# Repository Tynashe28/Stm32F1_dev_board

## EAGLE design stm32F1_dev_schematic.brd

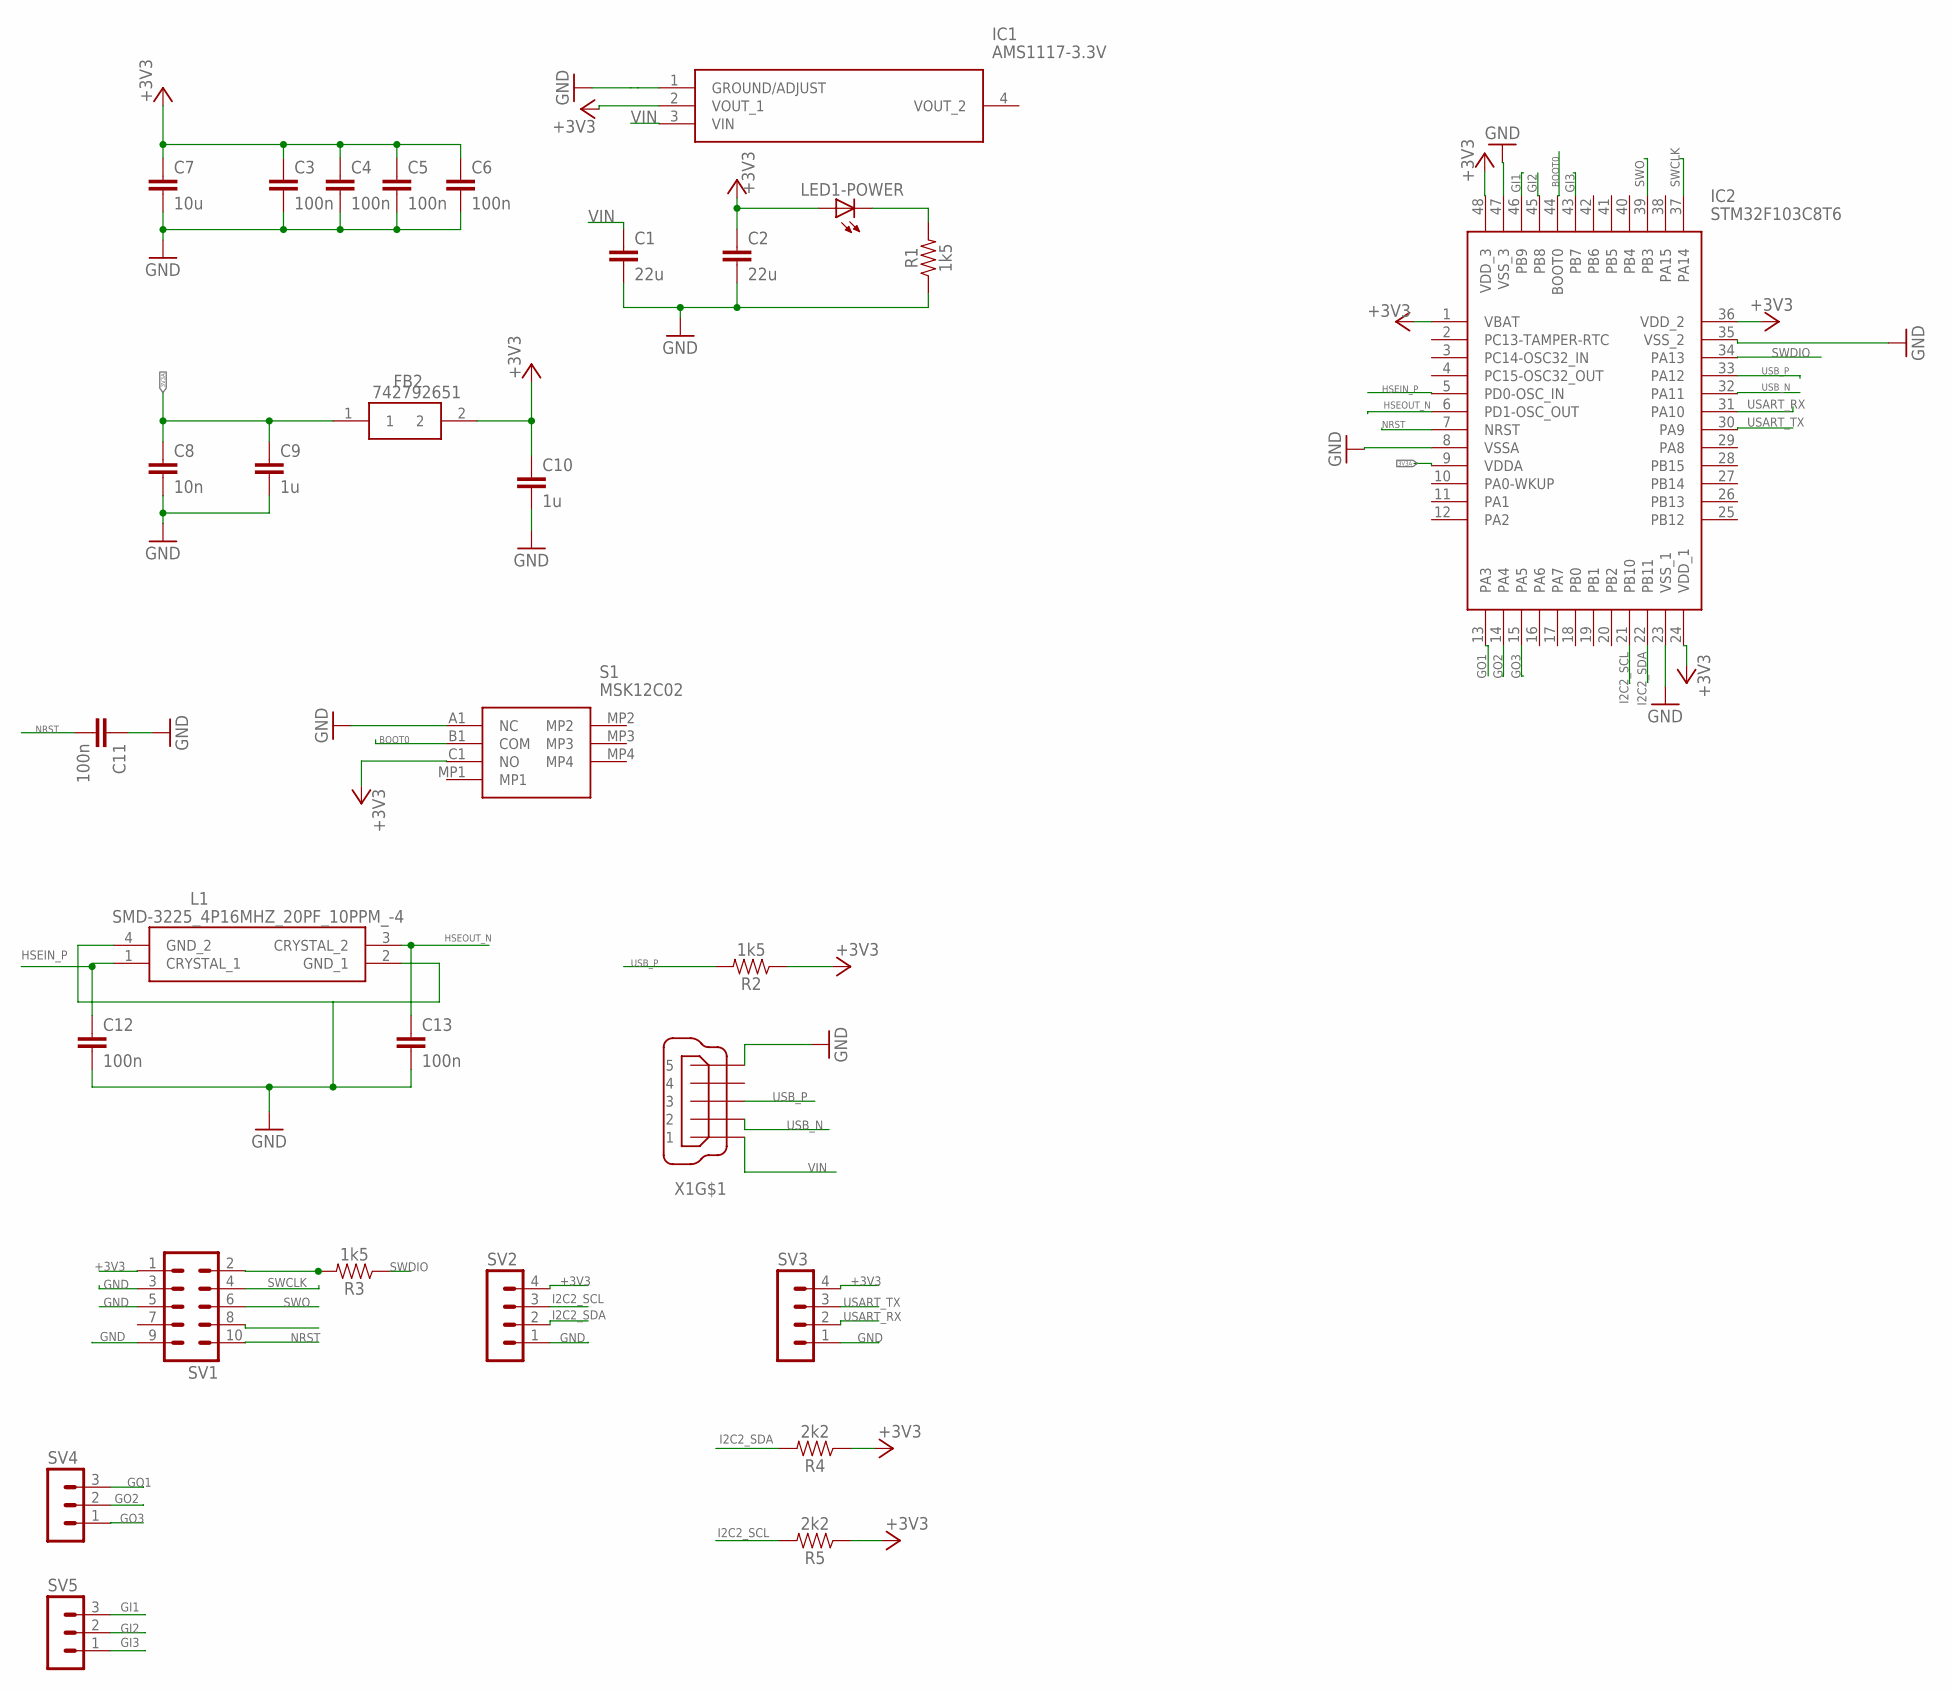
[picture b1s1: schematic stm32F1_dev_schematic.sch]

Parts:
C1, C2: 22u; 0805
C3, C4, C5, C6, C11, C12, C13: 100n; 0805
C7: 10u; 0805
C8: 10n; 0805
C9, C10: 1u; 0805
FB2: 742792651; BEADC1608X100N
IC1: AMS1117-3.3V; SOT229P700X180-4N
IC2: STM32F103C8T6; QFP50P900X900X160-48N
L1: SMD-3225_4P16MHZ_20PF_10PPM_-4; SMD3225_4P16MHZ20PF10PPM4085
LED1-POWER: LEDCHIPLED_0603; CHIPLED_0603
R1, R2, R3: 1k5; 0805
R4, R5: 2k2; 0805
S1: MSK12C02
SV1: MA05-2
SV2, SV3: MA04-1
SV4, SV5: MA03-1
X1: MINI-USB-SCHIELD-32005-301; 32005-301

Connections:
3V3A: C8.1, C9.1, FB2.1, IC2.9 (VDDA)
+3V3: C2.1, C3.1, C4.1, C5.1, C6.1, C7.1, C10.1, FB2.2, IC1.2 (VOUT_1), IC2.1 (VBAT), IC2.24 (VDD_1), IC2.36 (VDD_2), IC2.48 (VDD_3), LED1-POWER.A, R2.1, R4.1, R5.1, S1.C1 (NO), SV1.1, SV2.4, SV3.4
BOOT0: IC2.44 (BOOT0), S1.B1 (COM)
GI1: IC2.46 (PB9), SV5.3
GI2: IC2.45 (PB8), SV5.2
GI3: IC2.43 (PB7), SV5.1
GND: C1.2, C2.2, C3.2, C4.2, C5.2, C6.2, C7.2, C8.2, C9.2, C10.2, C11.1, C12.2, C13.2, IC1.1 (GROUND/ADJUST), IC2.8 (VSSA), IC2.23 (VSS_1), IC2.35 (VSS_2), IC2.47 (VSS_3), L1.2 (GND_1), L1.4 (GND_2), R1.1, S1.A1 (NC), SV1.3, SV1.5, SV1.9, SV2.1, SV3.1, X1.5
GO1: IC2.13 (PA3), SV4.3
GO2: IC2.14 (PA4), SV4.2
GO3: IC2.15 (PA5), SV4.1
HSEIN_P: C12.1, IC2.5 (PD0-OSC_IN), L1.1 (CRYSTAL_1)
HSEOUT_N: C13.1, IC2.6 (PD1-OSC_OUT), L1.3 (CRYSTAL_2)
I2C2_SCL: IC2.21 (PB10), R5.2, SV2.3
I2C2_SDA: IC2.22 (PB11), R4.2, SV2.2
unnamed: LED1-POWER.C, R1.2
unnamed: R3.2, SV1.2
NRST: C11.2, IC2.7 (NRST), SV1.10
SWCLK: IC2.37 (PA14), SV1.4
SWDIO: IC2.34 (PA13), R3.1
SWO: IC2.39 (PB3), SV1.6
USART_RX: IC2.31 (PA10), SV3.2
USART_TX: IC2.30 (PA9), SV3.3
USB_N: IC2.32 (PA11), X1.2
USB_P: IC2.33 (PA12), R2.2, X1.3
VIN: C1.1, IC1.3 (VIN), X1.1

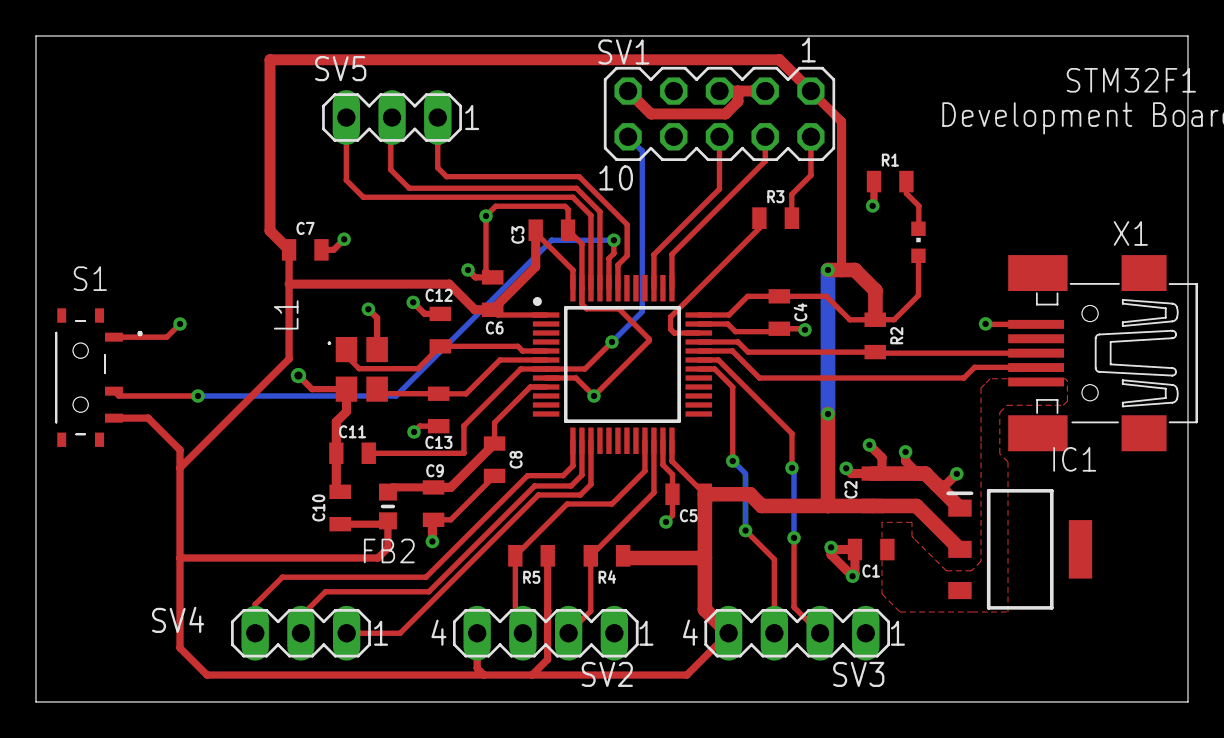
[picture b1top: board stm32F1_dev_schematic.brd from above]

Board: 2 copper layers, 64.0 x 37.0 mm, 30 parts (0 on the bottom side), 25 nets.

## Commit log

2022-07-15 initial Files
2022-07-15 added lib folder
2022-07-19 board done routing

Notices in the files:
parts and their libraries:
SparkFun-Capacitors: Licensing: Creative Commons ShareAlike 4.0 International - https://creativecommons.org/licenses/by-sa/4.0
